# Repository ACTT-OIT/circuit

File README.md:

# one-tenth-size-autonomous-car-circuit
自動運転技術の教育と研究を目的とした, 小型自動運転車"ACT (Autonomous Car Technologies)"の回路図ソースです.

使用部品は今後公開していきます.

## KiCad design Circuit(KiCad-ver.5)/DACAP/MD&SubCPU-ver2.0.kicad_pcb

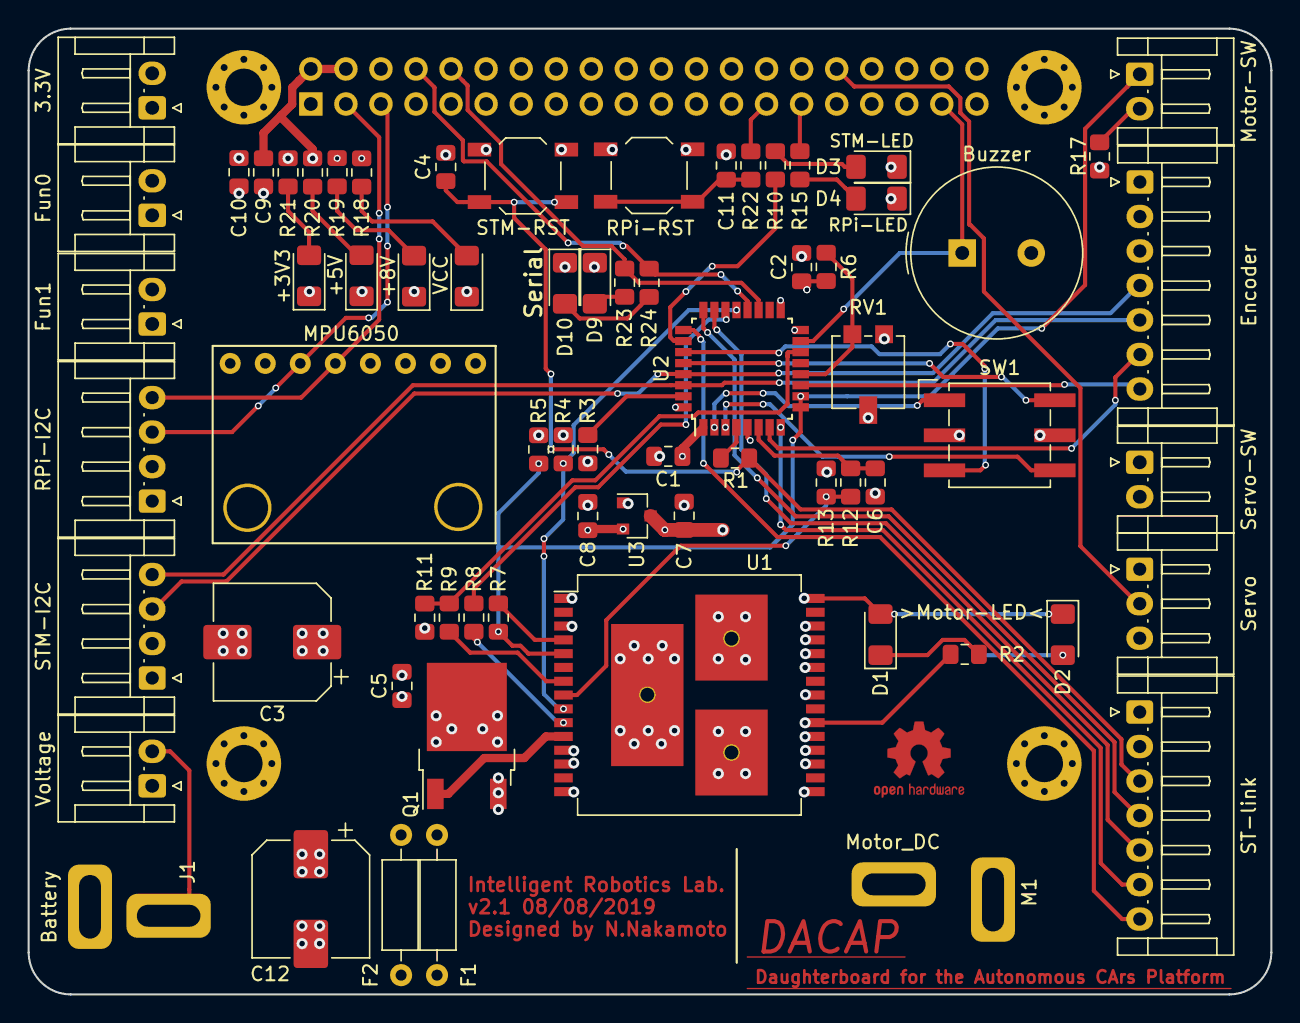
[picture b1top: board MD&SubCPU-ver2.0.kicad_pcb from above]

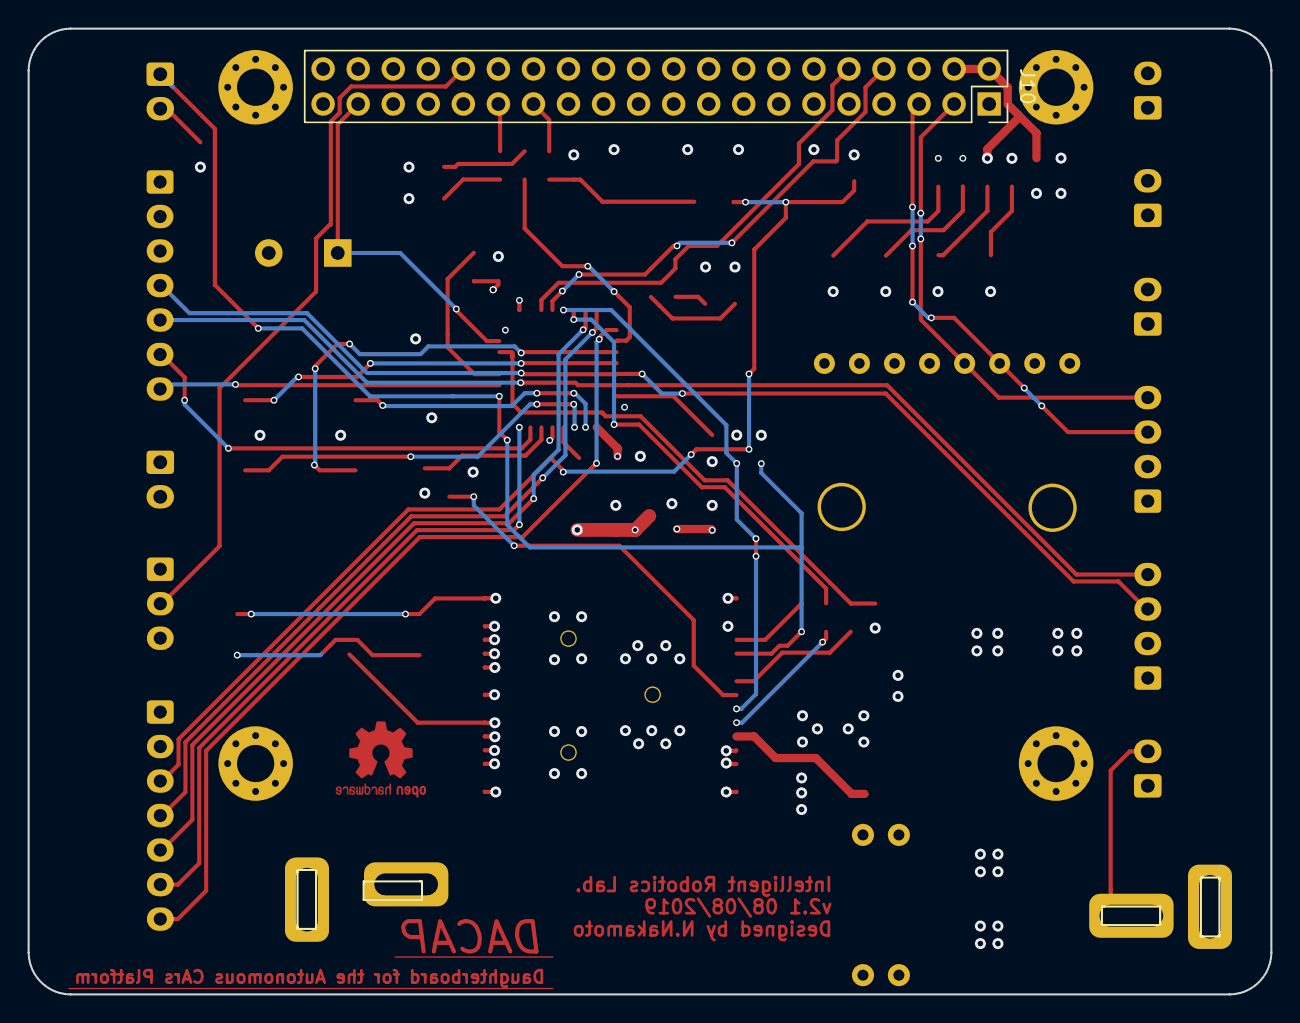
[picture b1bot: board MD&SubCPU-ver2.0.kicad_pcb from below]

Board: 4 copper layers, 90.0 x 70.0 mm, 74 parts (3 on the bottom side), 56 nets.

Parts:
3.3V: 3V3; JST_EH_S02B-EH_1x02_P2.50mm_Horizontal
Buzzer: PKM13EPYH4000-A0; Buzzer_TDK_PS1240P02BT_D12.2mm_H6.5mm
C1, C2, C4, C5, C6, C9, C10, C11: 0.1uF; C_0805_2012Metric_Pad1.15x1.40mm_HandSolder
C3, C12: 220uF; CP_Elec_8x10
C7, C8: 1uF; C_0805_2012Metric_Pad1.15x1.40mm_HandSolder
D1, D9: Red-LED; LED_1206_3216Metric_Pad1.42x1.75mm_HandSolder
D2, D10: Blue-LED; LED_1206_3216Metric_Pad1.42x1.75mm_HandSolder
D3, D4: Green-LED; LED_1206_3216Metric_Pad1.42x1.75mm_HandSolder
D5: VCC; LED_1206_3216Metric_Pad1.42x1.75mm_HandSolder
D6: +8V; LED_1206_3216Metric_Pad1.42x1.75mm_HandSolder
D7: +5V; LED_1206_3216Metric_Pad1.42x1.75mm_HandSolder
D8: +3V3; LED_1206_3216Metric_Pad1.42x1.75mm_HandSolder
Encoder: Encoder; JST_EH_S07B-EH_1x07_P2.50mm_Horizontal
F1, F2: Polyfuse; R_Axial_DIN0207_L6.3mm_D2.5mm_P10.16mm_Horizontal
Fun0: Fun0; JST_EH_S02B-EH_1x02_P2.50mm_Horizontal
Fun1: Fun1; JST_EH_S02B-EH_1x02_P2.50mm_Horizontal
H1, H2, H3, H4: MountingHole; MountingHole_2.7mm_M2.5_Pad_Via
J1: Battery; Ultra_male
J10: Raspberry_Pi_2_3; PinSocket_2x20_P2.54mm_Vertical
M1: Motor_DC; Ultra_female
MPU6050: MPU6050; MPU9250-BMP280
Motor-SW: Motor-ONOFF; JST_EH_S02B-EH_1x02_P2.50mm_Horizontal
Q1: IPD30N03S2L20ATMA1CT-ND; TO-252-2
R1, R22: 100; R_0805_2012Metric_Pad1.15x1.40mm_HandSolder
R2: 4.7k; R_0805_2012Metric_Pad1.15x1.40mm_HandSolder
R3, R6, R7, R8, R9, R10, R13, R15, R20, R21, R23, R24: 1k; R_0805_2012Metric_Pad1.15x1.40mm_HandSolder
R4, R5, R17, R18, R19: 2.2k; R_0805_2012Metric_Pad1.15x1.40mm_HandSolder
R11, R12: 10k; R_0805_2012Metric_Pad1.15x1.40mm_HandSolder
RPi-I2C: PI-I2C; JST_EH_S04B-EH_1x04_P2.50mm_Horizontal
RV1: 50k; Potentiometer_Vishay_TS53YL_Vertical
ST-link: ST-Link; JST_EH_S07B-EH_1x07_P2.50mm_Horizontal
STM-I2C: ST-I2C; JST_EH_S04B-EH_1x04_P2.50mm_Horizontal
SW1: CT3073-1-ND; Nidec_Copal_SH-7010B
SW2: STM-RST; SW_SPST_TL3342
SW3: RPi-RST; SW_SPST_TL3342
Servo: Servo; JST_EH_S03B-EH_1x03_P2.50mm_Horizontal
Servo-SW: Servo-ONOFF; JST_EH_S02B-EH_1x02_P2.50mm_Horizontal
U1: VNH5019A; ST_MultiPowerSO-30
U2: STM32F303K8T6; LQFP-32_7x7mm_P0.8mm
U3: MCP1703A-3302_SOT23; SOT-23
Voltage: voltmeter; JST_EH_S02B-EH_1x02_P2.50mm_Horizontal

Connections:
+3V3: 3.3V.2, C1.1, C2.1, C8.1, C10.1, Encoder.1, Encoder.2, J10.1, J10.17, MPU6050.1, R4.1, R5.1, R6.2, R21.1, RPi-I2C.2, ST-link.2, STM-I2C.2, U2.1, U2.5, U2.17, U3.2
+5V: C9.1, Fun0.2, Fun1.2, J10.2, J10.4, R20.1
+8V: F2.2, Q1.3, R19.1
+BATT: C12.1, F1.1, F2.1, J1.2, Voltage.2
CS: C6.1, R12.1, U2.6
Code0: SW1.1, U2.2
Code1: SW1.2, U2.3
Code2: SW1.4, U2.27
Code3: SW1.8, U2.28
ENA: Motor-SW.1, R5.2, R7.1, U1.5, U2.9, U2.10
ENB: R4.2, U1.9, U2.21
EncoderA: Encoder.6, U2.7
EncoderB: Encoder.7, U2.11
GND: 3.3V.1, Buzzer.2, C1.2, C2.2, C3.2, C4.2, C5.2, C6.2, C7.2, C8.2, C9.2, C10.2, C11.1, C12.2, D3.1, D4.1, D5.1, D6.1, D7.1, D8.1, D9.1, D10.1, Encoder.3, Fun0.1, Fun1.1, J1.1, J10.6, J10.9, J10.14, J10.20, J10.25, J10.30, J10.34, J10.39, MPU6050.2, R3.1, R11.2, R13.2, R17.2, RPi-I2C.1, RV1.2, RV1.3, ST-link.1, STM-I2C.1, SW1.C, SW2.1, SW3.2, Servo.1, U1.18, U1.19, U1.20, U1.26, U1.27, U1.28, U2.16, U2.32, U3.1, Voltage.1
INB: R8.1, U2.22
NRST: C4.1, R1.2, ST-link.3, SW2.2
unnamed: C11.2, R22.1, SW3.1
unnamed: D1.1, D2.2, R2.1
unnamed: D3.2, R10.2
unnamed: D4.2, R15.2
unnamed: D5.2, R18.2
unnamed: D6.2, R19.2
unnamed: D7.2, R20.2
unnamed: D8.2, R21.2
unnamed: D9.2, R23.2
unnamed: D10.2, R24.2
unnamed: J10.27, R22.2
unnamed: J10.29, R15.1
unnamed: Buzzer.1, J10.37, U2.15
unnamed: Motor-SW.2, R17.1
unnamed: Q1.1, U1.11
unnamed: R1.1, U2.4
unnamed: R3.2, U2.31
unnamed: R6.1, RV1.1, U2.12
unnamed: R7.2, U1.4
unnamed: R8.2, U1.10
unnamed: R9.2, U1.7
unnamed: R10.1, U2.26
unnamed: R12.2, R13.1, U1.8
OUTA: D1.2, D2.1, M1.1, U1.1, U1.25, U1.30, U1.33
OUTB: M1.2, R2.2, U1.15, U1.16, U1.21, U1.32
PI-SCL: J10.5, MPU6050.3, RPi-I2C.3
PI-SDA: J10.3, MPU6050.4, RPi-I2C.4
PWM: R9.1, R11.1, U2.14
ST-SCL: Encoder.4, STM-I2C.3, U2.29
ST-SDA: Encoder.5, STM-I2C.4, U2.30
SWCLK: ST-link.4, U2.24
SWDIO: ST-link.5, U2.23
Servo-sign: J10.32, Servo.2
UART_RXtoPI: J10.8, R24.1, U2.20
UART_TXtoPI: J10.10, R23.1, U2.19
VCC: C7.1, F1.2, R18.1, Servo-SW.2, U3.3
VCP_RX: ST-link.7, U2.25
VCP_TX: ST-link.6, U2.8
Vcc-servo: Servo.3, Servo-SW.1
Vout: C3.1, C5.1, Q1.2, U1.3, U1.12, U1.13, U1.23, U1.31

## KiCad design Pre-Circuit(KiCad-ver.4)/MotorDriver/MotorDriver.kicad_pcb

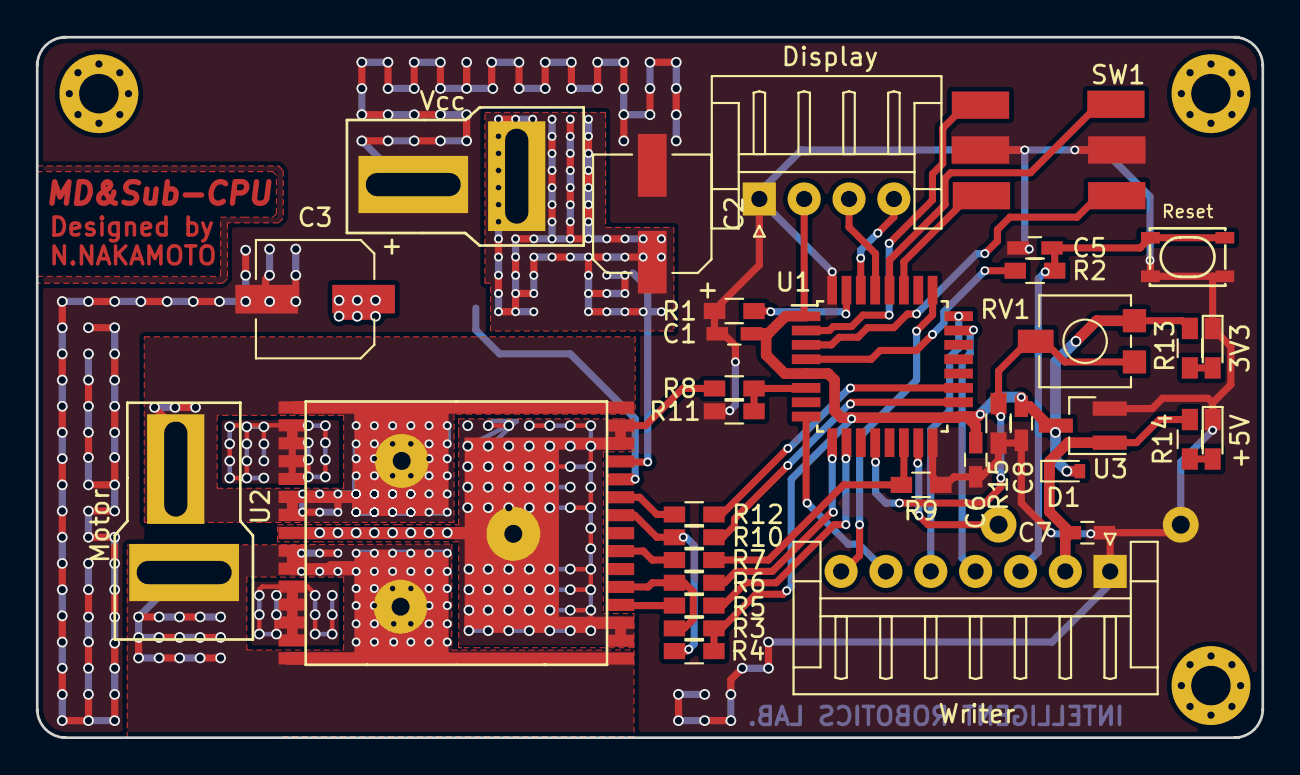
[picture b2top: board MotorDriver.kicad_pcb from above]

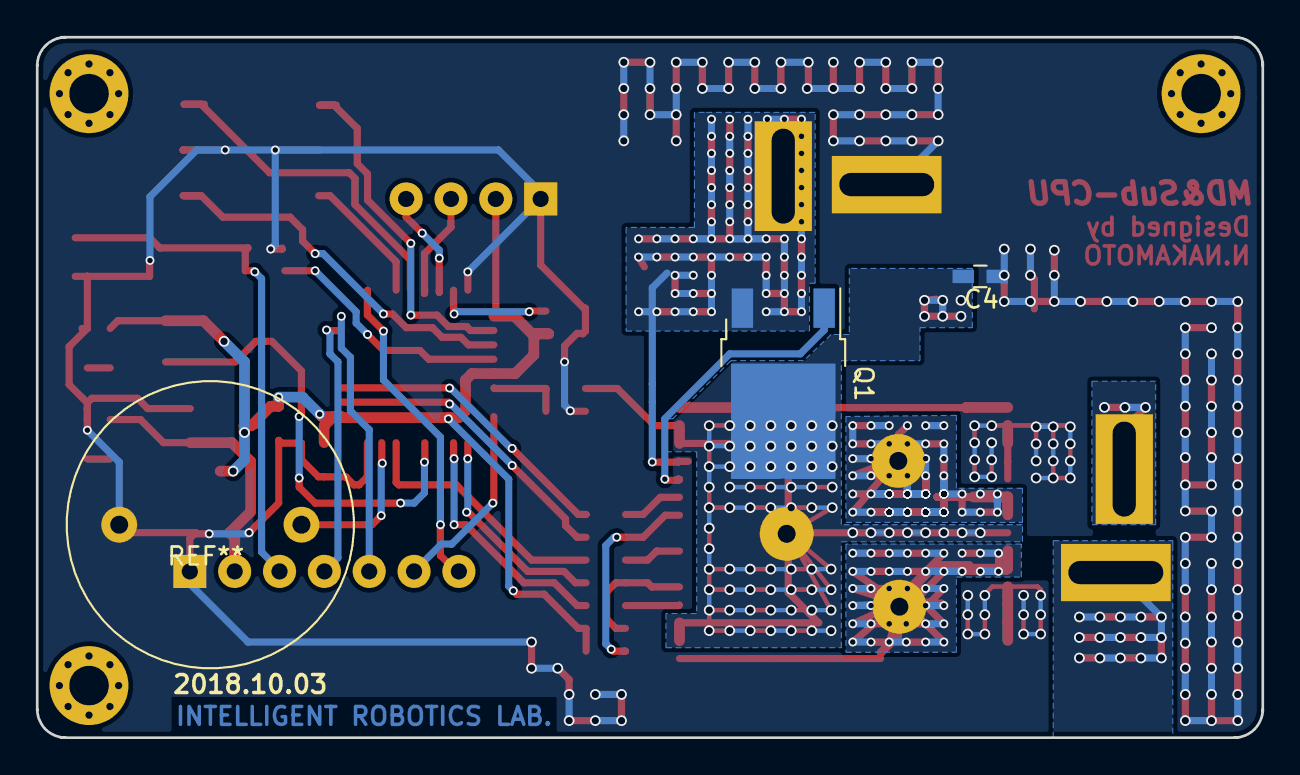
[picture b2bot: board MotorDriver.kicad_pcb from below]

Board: 2 copper layers, 68.3 x 39.1 mm, 37 parts (2 on the bottom side), 35 nets.

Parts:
3V3: LED; LED_0603_HandSoldering
+5V: LED; LED_0603_HandSoldering
C1, C4, C5, C6, C7: 0.1uF; C_0603_HandSoldering
C2, C3: 100uF; CP_Elec_6.3x5.8
C8: 10uF; C_0603_HandSoldering
D1: D_Schottky; D_0603
Display: display; JST_EH_S04B-EH_04x2.50mm_Angled
Motor: Motor; Ultra_conn
Q1: Q_NMOS_GDS; TO-252-2
R1, R9: 10k; R_0603_HandSoldering
R2: 100; R_0603_HandSoldering
R3, R4: 2k2; R_0603_HandSoldering
R5, R6, R7, R8, R10, R12, R13, R14, R15: 1k; R_0603_HandSoldering
R11: 560; R_0603_HandSoldering
RV1: POT; Potentiometer_Trimmer_Vishay_TS53YL
Reset: SW; SW_SKRPACE010
SW1: SW_Coded; Rotary-switch
U1: STM303K8T6; TQFP-32_7x7mm_Pitch0.8mm
U2: VNH5019A; VNH5019
U3: L7805; SOT-23_Handsoldering
Vcc: From Vcc; Ultra_conn
Writer: CONN_01X07; JST_EH_S07B-EH_07x2.50mm_Angled

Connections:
16_Code0: SW1.2, U1.2
16_Code1: SW1.3, U1.3
16_Code2: SW1.4, U1.27
16_Code3: SW1.5, U1.28
+3V3: C1.2, C6.1, C8.1, D1.2, Display.2, R3.2, R4.2, R13.2, RV1.1, U1.1, U1.5, U1.17, U3.3
+5V: C7.1, D1.1, R14.2, U3.1, Writer.2
CP: Q1.1, U2.11
ENA: R6.2, U1.9
ENB: R10.2, U1.18
GND: 3V3.1, +5V.1, C1.1, C2.2, C3.2, C4.2, C5.2, C6.2, C7.2, C8.2, Display.1, R1.1, R9.1, R11.1, R15.1, Reset.1, SW1.1, U1.16, U1.32, U2.17, U2.18, U2.19, U2.20, U2.26, U2.27, U2.28, U2.29, U3.2, Vcc.2, Writer.1
INA: R5.2, U1.10
INB: R12.2, U1.19
unnamed: 3V3.2, R13.1
unnamed: +5V.2, R14.1
unnamed: R1.2, U1.31
unnamed: R2.1, U1.4
unnamed: R3.1, R6.1, U2.5
unnamed: R5.1, U2.4
unnamed: R7.1, U2.7
unnamed: R4.1, R10.1, U2.9
unnamed: R8.1, R11.2, U1.6
unnamed: R12.1, U2.10
unnamed: R15.2, RV1.2, RV1.3, U1.12
OUTA: Motor.1, U2.1, U2.24, U2.25, U2.30, U2.31
OUTB: Motor.2, U2.15, U2.16, U2.21, U2.22, U2.32
PWM: R7.2, R9.2, U1.14
RESET: C5.1, R2.2, Reset.2, Writer.3
SCL: Display.3, U1.29
SDA: Display.4, U1.30
SWCLK: U1.24, Writer.5
SWDIO: U1.23, Writer.4
VCC: C2.1, Q1.3, U2.12, Vcc.1
VCP_RX: U1.25, Writer.7
VCP_TX: U1.8, Writer.6
Vout: C3.1, C4.1, Q1.2, R8.2, U2.2, U2.3, U2.13, U2.14, U2.23, U2.33

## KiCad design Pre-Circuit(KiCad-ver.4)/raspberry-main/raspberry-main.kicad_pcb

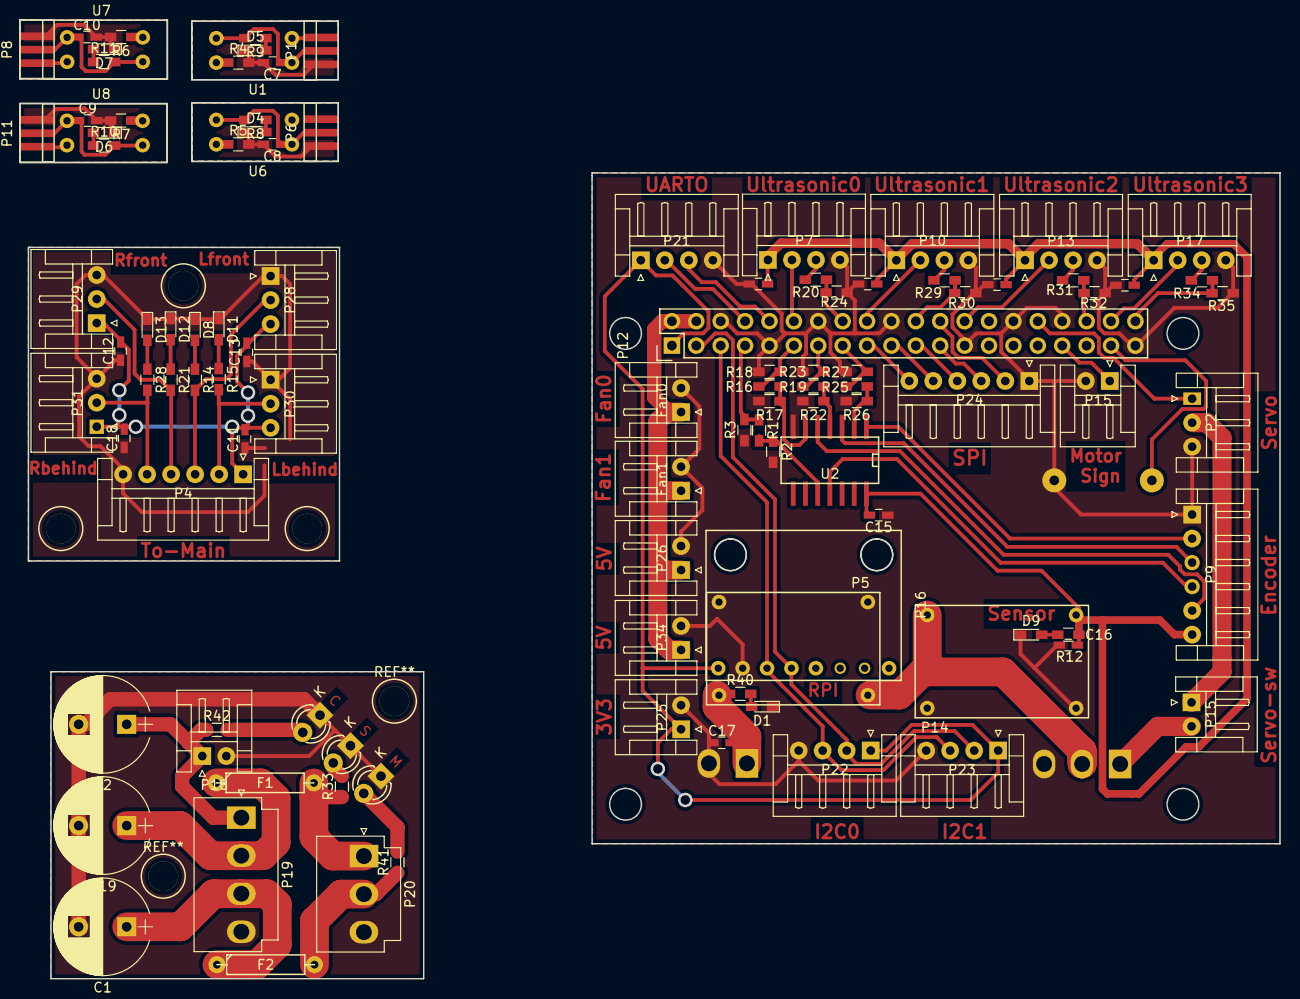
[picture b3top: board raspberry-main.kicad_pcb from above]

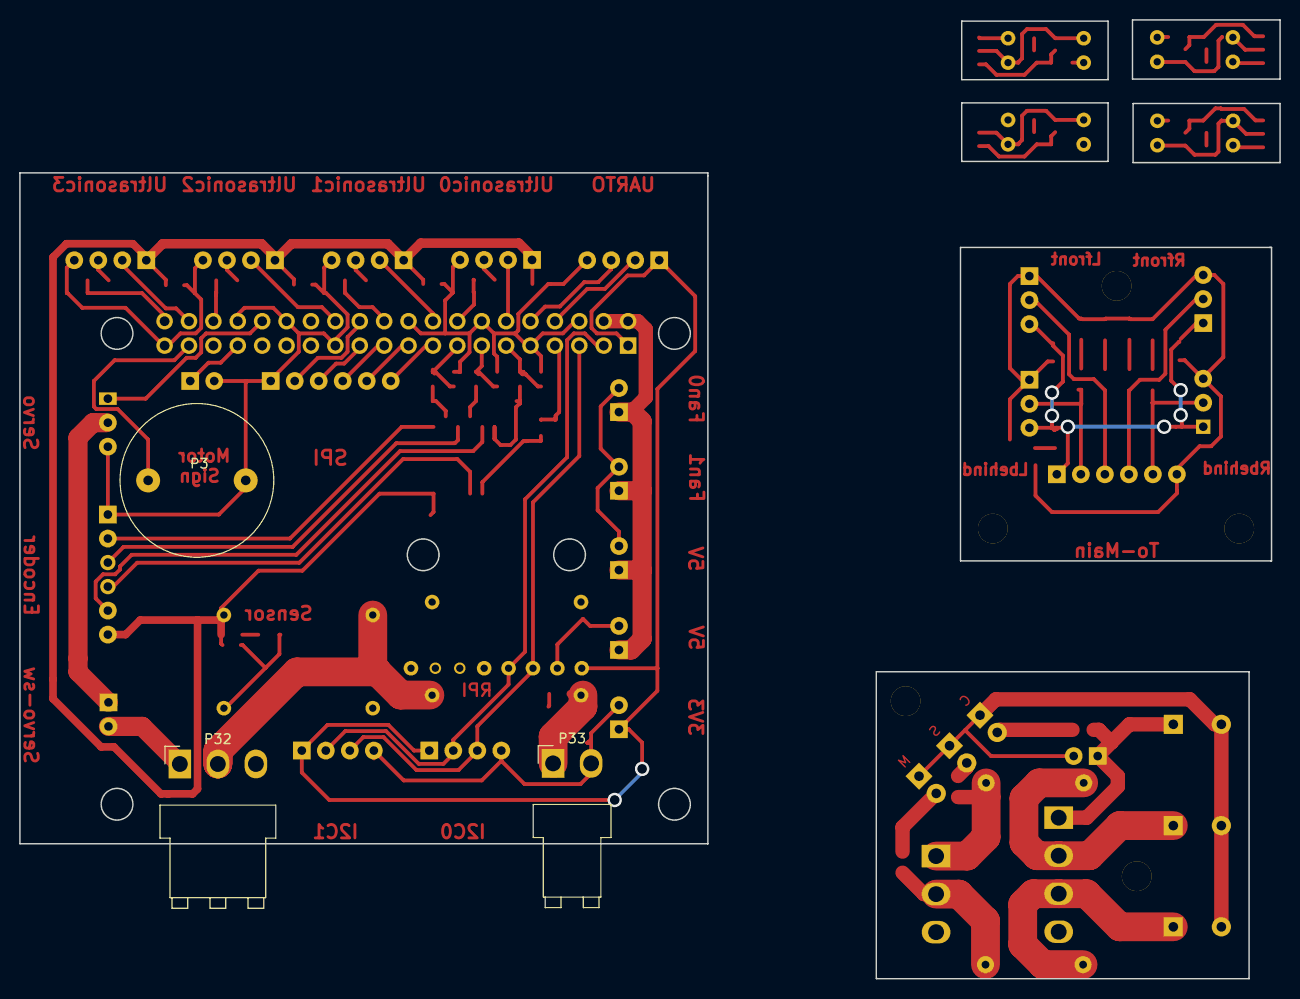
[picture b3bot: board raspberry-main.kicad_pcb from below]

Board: 2 copper layers, 131.2 x 99.8 mm, 107 parts (3 on the bottom side), 65 nets.

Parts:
C1, C2, C19: 470u; CP_Radial_D10.0mm_P5.00mm
C7, C8, C9, C10, C11, C12, C13, C15, C16, C17, C18: 0.1u; C_0603_HandSoldering
D1: DCDC-LED-pi; LED_0603_HandSoldering
D4, D5, D6, D7, D8, D11, D12, D13: LED; LED_0603_HandSoldering
D9: DCDC-LED-sen; LED_0603_HandSoldering
F1, F2: Fuse; R4-LARGE_PADS
Fan0, Fan1: 5V; JST_EH_S02B-EH_02x2.50mm_Angled
Main: 3mmLED; LED-3MM
P1: L-front; ZH-3pin-SMD
P2: Servo; JST_EH_S03B-EH_03x2.50mm_Angled
P3: Buzzer; BUZZER
P4: E(base)-to-Main; JST_EH_S06B-EH_06x2.50mm_Angled
P5: DC/DC-MP2307-pi; MP2307
P6: L-behind; ZH-3pin-SMD
P7: Ultrasonic0; JST_EH_S04B-EH_04x2.50mm_Angled
P8: R-front; ZH-3pin-SMD
P9: E-to-Main(base); JST_EH_S06B-EH_06x2.50mm_Angled
P10: Ultrasonic1; JST_EH_S04B-EH_04x2.50mm_Angled
P11: R-behind; ZH-3pin-SMD
P12: Raspberry Pi; Pin_Header_Straight_2x20
P13: Ultrasonic2; JST_EH_S04B-EH_04x2.50mm_Angled
P14: DC/DC-MP2307-sensor; MP2307
P15: Servo-sw; JST_EH_S02B-EH_02x2.50mm_Angled
P15#2: Motor-Sign; JST_EH_S02B-EH_02x2.50mm_Angled
P16: MCP6050; MPU6050
P17: Ultrasonic3; JST_EH_S04B-EH_04x2.50mm_Angled
P18: Volteage Checker; JST_EH_S02B-EH_02x2.50mm_Angled
P19: Battery; JST_VH_B4P-VH_4x3.96mm_Vertical
P20: Main&Servo0; JST_VH_B3P-VH-B_3x3.96mm_Vertical
P21: UARTO; JST_EH_S04B-EH_04x2.50mm_Angled
P22: I2C-0; JST_EH_S04B-EH_04x2.50mm_Angled
P23: I2C-1; JST_EH_S04B-EH_04x2.50mm_Angled
P24: SPI; JST_EH_S06B-EH_06x2.50mm_Angled
P25: 3V3; JST_EH_S02B-EH_02x2.50mm_Angled
P26, P34: 5V; JST_EH_S02B-EH_02x2.50mm_Angled
P28: L-front; JST_EH_S03B-EH_03x2.50mm_Angled
P29: R-front; JST_EH_S03B-EH_03x2.50mm_Angled
P30: L-behind; JST_EH_S03B-EH_03x2.50mm_Angled
P31: R-behind; JST_EH_S03B-EH_03x2.50mm_Angled
P32: Main&Servo1; JST_VH_B3PS-VH_2x3x3.96mm_Horizontal
P33: To-USB; JST_VH_B2PS-VH_2x2x3.96mm_Horizontal
R1, R16, R19, R20, R25, R29, R31, R34: 3.3k; R_0603_HandSoldering
R2, R3, R17, R18, R22, R23, R24, R26, R27, R30, R32, R35: 4.7k; R_0603_HandSoldering
R4, R5, R6, R7, R33, R41, R42: 470; R_0603_HandSoldering
R8, R9, R10, R11, R12, R14, R15, R21, R28, R40: 150; R_0603_HandSoldering
Servo: 3mmLED; LED-3MM
U1, U6, U7, U8: PHOTOINTERRUPT; photo-interruptor
U2: 74HC14; SOIC-14_N_long
Vol: 3mmLED; LED-3MM

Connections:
+3V3: P12.1, P12.17, P16.1, P21.1, P22.1, P23.1, P24.6, P25.1
+5V: C7.1, C8.1, C9.1, C10.1, C11.2, C12.2, C13.2, C15.2, C16.2, C18.2, P1.2, P4.1, P6.2, P7.1, P8.2, P9.6, P10.1, P11.2, P13.1, P14.3, P17.1, P28.3, P29.1, P30.3, P31.1, R8.2, R9.2, R10.2, R11.2, R12.1, U1.1, U1.3, U2.14, U6.1, U6.3, U7.1, U7.3, U8.1, U8.3
+5VD: C17.2, Fan0.1, Fan1.1, P5.3, P12.2, P12.4, P26.1, P33.1, P34.1, R40.1
/Main-VCC: C1.1, F2.1, P5.1, P14.1, P19.3, P32.2
/Servo-VCC: C19.1, F1.1, P2.2, P15.1, P15.2, P19.2, P32.1
/Voltage-Checker-VCC: C2.1, P18.1, P19.1, R42.1
Echo1: P12.16, R20.2, R24.1
Echo2: P12.22, R29.2, R30.1
Echo3: P12.36, R31.2, R32.1
Echo4: P12.40, R34.2, R35.1
GND: C1.2, C2.2, C7.2, C8.2, C9.2, C10.2, C11.1, C12.1, C13.1, C15.1, C16.1, C17.1, C18.1, C19.2, D1.1, D4.1, D5.1, D6.1, D7.1, D8.1, D9.1, D11.1, D12.1, D13.1, Fan0.2, Fan1.2, Main.1, P1.1, P2.3, P3.2, P4.6, P5.2, P5.4, P6.1, P7.4, P8.3, P9.1, P10.4, P11.3, P12.6, P12.9, P12.14, P12.20, P12.25, P12.30, P12.34, P12.39, P13.4, P14.2, P14.4, P15#2.2, P16.2, P17.4, P18.2, P19.4, P20.3, P21.4, P22.4, P23.4, P24.1, P25.2, P26.2, P28.1, P29.3, P30.1, P31.3, P32.3, P33.2, P34.2, R2.2, R3.2, R4.2, R5.2, R6.2, R7.2, R17.2, R18.2, R22.2, R23.2, R24.2, R26.2, R27.2, R30.2, R32.2, R35.2, Servo.1, U2.7, Vol.e1
In-L-behind: P4.2, P6.3, P30.2, R15.2, U6.4
In-L-front: P1.3, P4.3, P28.2, R14.2, U1.4
In-R-behind: P4.5, P11.1, P31.2, R28.2, U8.4
In-R-front: P4.4, P8.1, P29.2, R21.2, U7.4
L-b: P9.5, U2.5
L-f: P9.4, U2.11
M-sign: P12.33, P15#2.1
MISO: P12.21, P24.4
MOSI: P12.19, P24.5
unnamed: D1.2, R40.2
unnamed: D4.2, R8.1
unnamed: D5.2, R9.1
unnamed: D6.2, R10.1
unnamed: D7.2, R11.1
unnamed: D8.2, R14.1
unnamed: D9.2, R12.2
unnamed: D11.2, R15.1
unnamed: D12.2, R21.1
unnamed: D13.2, R28.1
unnamed: Main.2, R33.2
unnamed: R41.2, Servo.2
unnamed: R42.2, Vol.2
unnamed: F1.2, P20.1, R33.1
unnamed: F2.2, P20.2, R41.1
unnamed: P7.3, R20.1
unnamed: P10.3, R29.1
unnamed: P3.1, P12.37
unnamed: P13.3, R31.1
unnamed: P17.3, R34.1
unnamed: R1.2, R2.1, U2.10
unnamed: R4.1, U1.2
unnamed: R5.1, U6.2
unnamed: R6.1, U7.2
unnamed: R7.1, U8.2
unnamed: R16.2, R17.1, U2.6
unnamed: R19.2, R22.1, U2.4
unnamed: R25.2, R26.1, U2.2
Out-L-behind: P12.11, R16.1, R18.1
Out-L-front: P12.7, R1.1, R3.1
Out-R-behind: P12.15, R25.1, R27.1
Out-R-front: P12.13, R19.1, R23.1
R-b: P9.2, U2.1
R-f: P9.3, U2.3
S-sign: P2.1, P12.32
SC: P12.24, P24.2
SCL: P12.5, P16.3, P22.3, P23.3
SCLK: P12.23, P24.3
SDA: P12.3, P16.4, P22.2, P23.2
Trig1: P7.2, P12.12
Trig2: P10.2, P12.18
Trig3: P12.26, P13.2
Trig4: P12.38, P17.2
UARTO-Rx: P12.10, P21.3
UARTO-Tx: P12.8, P21.2

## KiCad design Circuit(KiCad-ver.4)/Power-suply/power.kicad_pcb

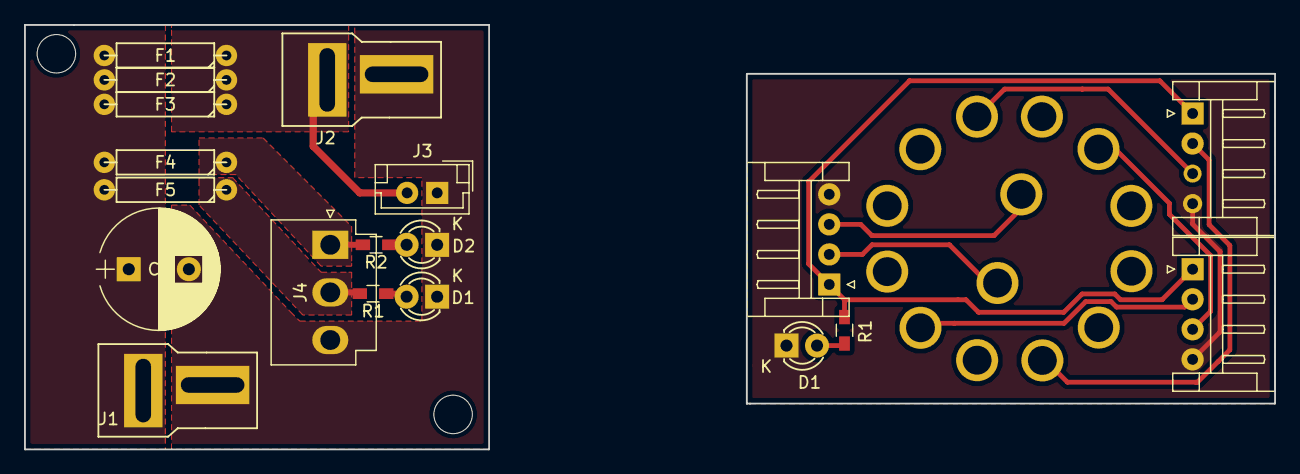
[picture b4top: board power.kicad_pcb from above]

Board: 2 copper layers, 104.0 x 35.3 mm, 20 parts (1 on the bottom side), 16 nets.

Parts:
C9: 470uF; CP_Radial_D10.0mm_P5.00mm
D1, D1#2, D2: LED; LED-3MM
F1, F2, F3, F4, F5: Fuse; Fuse-p-sup
J1: Battery; Ultra_conn
J2: R-pi; JST_EH_S04B-EH_04x2.50mm_Angled
J2#2: To MD; Ultra_conn
J3: PC; JST_EH_S04B-EH_04x2.50mm_Angled
J3#2: JST_EH_B02B-EH-A_02x2.50mm_Straight
J4: Servo r-pi; JST_VH_B3P-VH-B_3x3.96mm_Vertical
J7: ST-Link; JST_EH_S04B-EH_04x2.50mm_Angled
R1, R1#2, R2: 1k; R_0603_HandSoldering
SW1: SW_Rotary2x6; Rotary-4x3

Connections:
+5VA: J2.1, J3.1, J7.1, R1#2.2
D+a: J2.3, SW1.7
D+d: J3.3, SW1.9
D-a: J2.2, SW1.1
D-d: J3.2, SW1.3
GND: C9.2, D1.1, D2.1, J1.2, J2#2.2, J3#2.1, J4.3
GNDA: D1#2.1, J2.4, J3.4, J7.4
unnamed: C9.1, F1.2, F2.2, F3.2, F4.2, F5.2, J1.1
unnamed: D1.2, R1.1
unnamed: D2.2, R2.1
unnamed: D1#2.2, R1#2.1
unnamed: F1.1, F2.1, F3.1, J2#2.1, J3#2.2
unnamed: F4.1, J4.1, R2.2
unnamed: F5.1, J4.2, R1.2
unnamed: J7.2, SW1.13
unnamed: J7.3, SW1.14

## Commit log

2019-06-03 KiCadを用いた回路データ
2019-06-03 以前の回路データ
2019-06-03 再設計した回路データ
2019-08-23 upgrade circuit
